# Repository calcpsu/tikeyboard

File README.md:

# Keyboard for TI Majestic Series Calculators #

1970's TI calculatore keyboards are known for failure - squishy or dead keys - leading to premature death.
As the original keyboards are generally unrepairable, this is a replacement using a PCB and micro tactile switches.
Enjoy the use of technology advanced during the mobile phone era (0.8mm thickness tact switches!).

## Details: ##

The PCB + switch comes to 2.4mm thick, which is nearly identical to the original 2.2mm thick keyboard in these calculators.

Two versions are included:
* 5 Column x 8 Row: made for a TI45, but I understand should also fit a standard TI30
* 5 Column x 9 Row: suits a TI58, TI59 programmable

## Switch Type: ##

Switches are a reasonably common SMD type (Dimensions: 4.8mm x 4.8mm x 0.8mm) available from electrical component wholesalers and elsewhere online at low cost. There is another type with a metal top cover, often sold as '1.0mm' thick, but is likely identical button underneath. These work well too (and might be a bit more durable). As long as it matches the drawing below, it should be compatible.
Some sources (apologies if links expire):
* Digikey: [PTS526 SM08 SMTR2 LFS](https://www.digikey.com.au/short/9qb5pmcp)
* Aliexpress: [100 Pcs/lot Membrane Switch 4x4x 0.8MM 4X4X0.8mm Tactile Push Button Switch Tact 4 Pin 4*4*0.8mm Switch Micro Switch SMD](https://www.aliexpress.com/item/4001331647427.html) or [SJMS 100pcs Micro Tactile Push Button Touch Tact Waterproof Switch 4x4x1 SMD 4 Pin SMT 4*4*1.0 mm Ultra thin mini Switch](https://www.aliexpress.com/item/1005001828986512.html)
* Amazon: [eMagTech 50pcs 4 Pin Patch Tact Switch Tactile Switch for Car Remote Control Key 4.8x4.8x0.8mm 4 Pin Tactile Push Button Switch Metal Plastic Switch](https://www.amazon.com.au/eMagTech-Tactile-Control-4-8x4-8x0-8mm-Plastic/dp/B0CN9467VQ)

## How to: ##

Before committing to replacing your keyboard, please consider the risks involved in working on ancient electronics. Components are sensitive to ESD, plastics and PCBs are old and susceptible to mechanical damage (hairline cracking you may not even see!). If damaged, replacement parts are typically not available at all, so damage can be irrepairable. While I have successfully replaced the keyboards on a number of my calculators, I've lost at least one calculator to ESD death during a (not keyboard related) repair attempt. As such, I cannot provide any guarantees of success but I do wish you the best of luck if you do choose to proceed. The below instructions are provided for you to undertake at your own risk.

### Building the keyboard: ###
1. Solder the tact switches to the PCB. Ensure they are accurately located (use the silkscreen layout), and flat on the PCB.
   - The switches are small and are easy to overheat when soldering - which can damage and change the feel. Use a temperature controlled iron and try to limit the heat you apply!
   - The switches need to be flat on the board, if they are raised (which can occur when soldering), the buttons will have inconsistent feel.
   - I have had some success using a tiny dab of superglue applied with a needle to locate the switches prior to soldering.
   - Do not press the switches down with any sharp objects (tweezers, screwdrivers, etc.) - this can deform the dome and again, result in inconsistent feel.
2. Solder 50mm (2in) approx. lead wires (I use copper strands from 2.5mm^2 house wiring) to each wire header, on the front (key) side of the board, extending upwards. _Note: for TI-59, the leadwires can be shorter (about 15mm is plenty)._

_Note: for Rev0, I made an error with the offset of two of the pins (R3 and R8), which is easily corrected with the lead wires. Rev1 of the board has this fixed, so it's a direct match for the original._

### Installation (Majestic series TI30/TI55/Programmer/TI45 and similar): ###
_Note: These calculators have early MOS ICs, which have no or minimal ESD protection in comparison to modern ICs. It is more important to take precautions than you might be used to with modern electronics!. Use an ESD mat and strap if you have one._
1. Open the calculator case: unclip the clips inside the battery compartment with a narrow ruler or wide screwdriver, and then push the rear case part downwards to separate front and back.
2. Desolder the original keyboard at the main board.
3. Assemble into the calculator, align all the lead wires and insert into the main board. It is imporatant to ensure the lead wires are bent/routed as per the original keyboard so the case will fit back together. This varies between calculator types.
4. Solder lead wires to main board, and trim.
5. Reassemble calculator.

### Installation (TI59 and similar): ###
The TI59 is a more complex calculator - the below instructions worked for me, please do get in touch via issues or email if you have any questions or problems.
_Note: These calculators have early MOS ICs, which have no or minimal ESD protection in comparison to modern ICs. It is more important to take precautions than you might be used to with modern electronics!. Use an ESD mat and strap if you have one._
1. Remove battery
2. Open calculator case by unscrewing the two fasteners on the back. Unclip the back case by lifting the back slightly, and sliding the back part of the case downwards to releasee the clips at the bottom.
3. Remove 2x flex cables from the card reader, noting how these are routed around the components and case.
4. Remove 4x screws from the card reader.
5. Remove the card reader and power switch by lifting out.
6. Use a small screwdriver to push up the two keyboard clips at the top of the keyboard via the cutouts in the mainboard.
7. Lift the mainboard and keyboard out from the top: take care not to lose any keys (they are loose!). Clean up as much crumbled foam as you can from the keyboard area.
8. Place the new foam pad over the keys.
9. Carefully desolder the 14 keyboard wires from the mainboard and remove the keyboard, ensuring you repair any damaged tracks and clean up flux residue (I use IPA and lots of q-tips).
10. Remove the black plastic spacer from the back of the keyboard.
11. Cut off the small locating pins from the black spacer, and sand or file these completely flush.
12. Locate the black spacer on the mainboard, and fix in place for reassembly with a very small amount of glue (e.g. superglue).
13. Fit the new keyboard to the mainboard, **leaving the wires unsoldered for the moment.**
14. Install the keyboard and mainboard into the front part of the case - slot the bottom of both in first, and gently press down the top until clipped in. Press around the mainboard to make sure everything is seated correctly.
15. Reinstall the card reader with 4x screws.
16. Check the action of the buttons, if feels ok continue, otherwise disassemble again (remove keyboard/mainboard) and see keyboard fit adjustment below.
17. Reinstall the flex cables for the card reader. Ensure the flex cable is routed correctly (as you noted previously).
18. Reinstall the back of the case by slotting into the bottom, and pressing up and down over. Take care not to damage the flex cables or components on the mainboard while doing so.
19. Reinstall the two screws on the back of the case.
20. Check the action of the buttons, if feels ok continue, otherwise disassemble again and see keyboard fit adjustment below.
21. Now solder a few of the keyboard leadwires, accessing through the back of the battery compartment. You don't need to solder them all, just enough to make sure the relative position of the keyboard and mainboard is locked in.
22. Now remove the back of the case and card reader flex cables, so you can solder and trim all the rest of the keyboard leadwires.
23. Reinstall the card reader flex cables, reinstall the back of the case.
24. Reinstall the battery (or connect to 3.3-5.0V power supply, taking care with polarity, which is marked on the mainboard) and test the keyboard/calculator works!

#### Keyboard Fit Adjustment ###
The keyboard is obviously not an exact copy of the original. The action of the small buttons is shorter than the original keyboard, and is slightly less tolerant to fit. You can adjust the fit through a number of methods, to address the two main possible problems:
1. Keys are squished with reassembly of the back of the case, and constantly pressed (particularly bottom row):
   a. Add tape or foam pieces to the front of the keyboard, to apply more pressure between the case front and the keyboard in the affected location.
   b. Make sure the spacer between the keyboard and mainboard locating posts are completely flat / fully removed. You may want to sand the spacer flat (fine - 320 grit or higher - sandpaper on the bench, rub the spacer on this a few times and observe progress until area around each pin is visibly abraded).
   c. File/sand the posts in the rear part of the case that go through the mainboard and contact the keyboard, to reduce pressure from the back of the case in the relevant locations (e.g. for bottom row issues, focus on the ones at the bottom of the case back). Don't go too far, or the key action may become loose.
2. Keys rattle or feel loose (you may have gone too far with one of the above steps):
   a. Make sure you have put that black spacer between the keyboard and mainboard. It's necessary to fully support the keyboard against the pressure from the foam pad.
   b. Apply tape or foam to the back of the keyboard in key locations (where the case back posts contact and support the keyboard) to increase pressure toward the front of the case.
   c. Consider a thicker foam pad between the keys (although this can increase the force required to press keys). It is unlikely you'll want more than 1.5mm.

## Replacing the foam:

The foam layer between the keycaps and the switches is significant to maintain the feel of the keypad. Without it, the keycaps rattle and the key feel is plasticky. It is often crumbly and degraded with age. It can be replaced with a slice of 1mm EVA foam, again widely available from craft stores and online:
* [NEW 1pcs Thickness 1/2/3/5/10mm Eva Foam Sheets Sound-Absorbing Noise Spone Foam Craft Eva Sheets Handmade Model Making Material](https://www.aliexpress.com/item/1005005567697486.html)

## Requests & PCBs:

Please do let me know if you have requests for further types.
And if you'd like a PCB or a built one, let me know - happy to provide bare PCBs, kits or assembled keyboards (to order).

Contact me at: info@calcpsu.com.au

## License

As per below, you are welcome to reproduce, amend, modify for personal use & friends.
I request you do not use this design for commercial production - i.e. no retail listings please. I'll give you a pass for a 'batch' where costs are shared.

This work is licensed under a
[Creative Commons Attribution-NonCommercial-ShareAlike 4.0 International License][cc-by-nc-sa].

[![CC BY-NC-SA 4.0][cc-by-nc-sa-image]][cc-by-nc-sa]

[cc-by-nc-sa]: http://creativecommons.org/licenses/by-nc-sa/4.0/
[cc-by-nc-sa-image]: https://licensebuttons.net/l/by-nc-sa/4.0/88x31.png
[cc-by-nc-sa-shield]: https://img.shields.io/badge/License-CC%20BY--NC--SA%204.0-lightgrey.svg

## The paitent: ##
A TI-45, the only Majestic with a VFD display, available in the European market.
Unusual, as most of this series had LED displays.

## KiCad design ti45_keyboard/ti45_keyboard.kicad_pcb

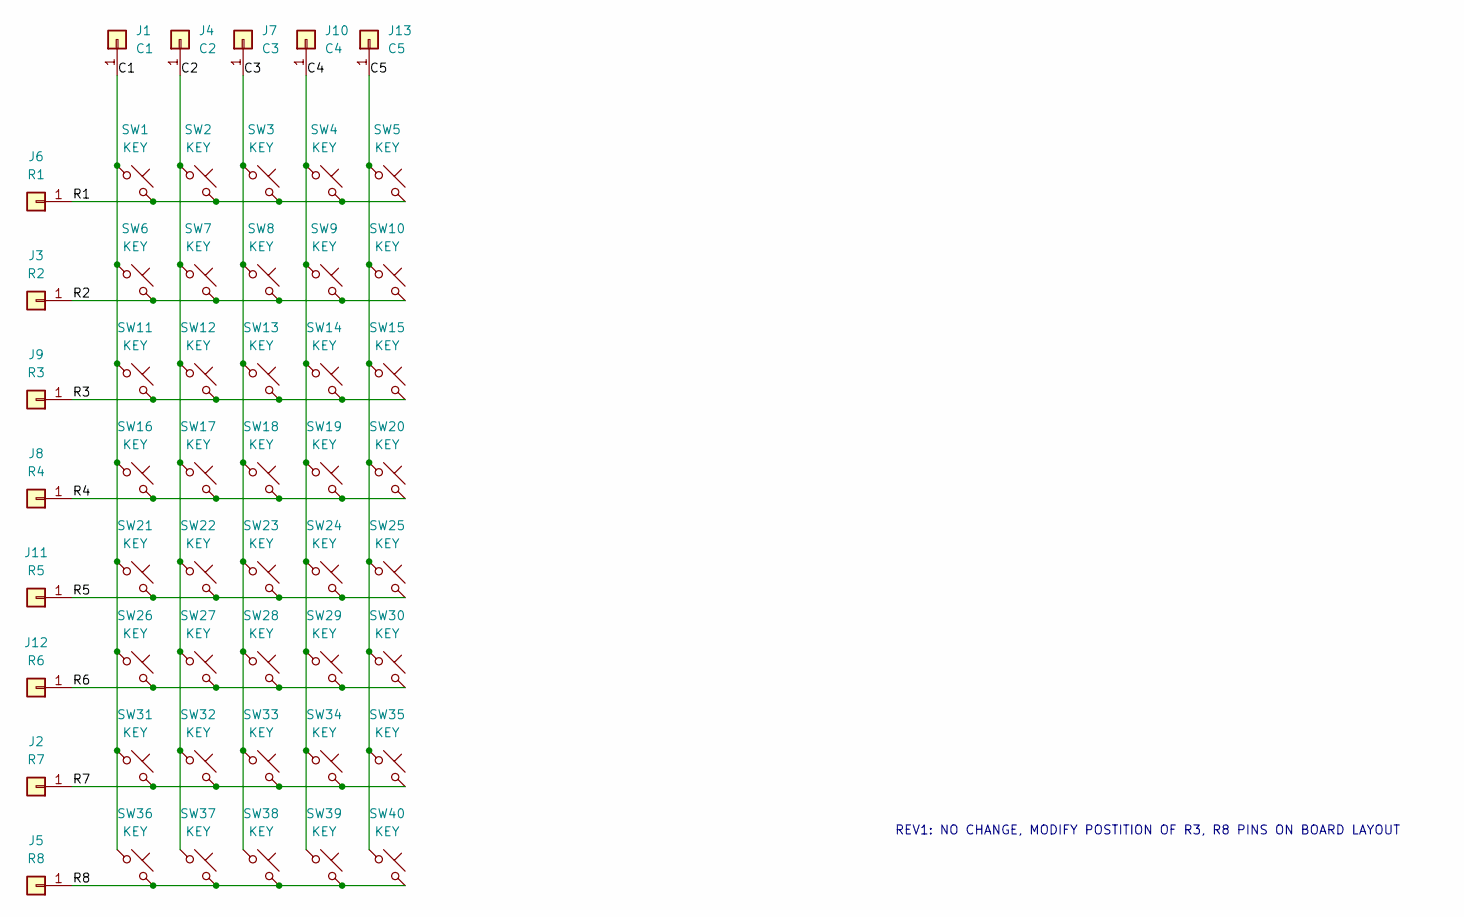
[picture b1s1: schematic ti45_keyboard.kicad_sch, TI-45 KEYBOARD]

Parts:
J1: C1; SolderWire-0.25sqmm_1x01_D0.65mm_OD1.7mm
J2: R7; SolderWire-0.25sqmm_1x01_D0.65mm_OD1.7mm
J3: R2; SolderWire-0.25sqmm_1x01_D0.65mm_OD1.7mm
J4: C2; SolderWire-0.25sqmm_1x01_D0.65mm_OD1.7mm
J5: R8; SolderWire-0.25sqmm_1x01_D0.65mm_OD1.7mm
J6: R1; SolderWire-0.25sqmm_1x01_D0.65mm_OD1.7mm
J7: C3; SolderWire-0.25sqmm_1x01_D0.65mm_OD1.7mm
J8: R4; SolderWire-0.25sqmm_1x01_D0.65mm_OD1.7mm
J9: R3; SolderWire-0.25sqmm_1x01_D0.65mm_OD1.7mm
J10: C4; SolderWire-0.25sqmm_1x01_D0.65mm_OD1.7mm
J11: R5; SolderWire-0.25sqmm_1x01_D0.65mm_OD1.7mm
J12: R6; SolderWire-0.25sqmm_1x01_D0.65mm_OD1.7mm
J13: C5; SolderWire-0.25sqmm_1x01_D0.65mm_OD1.7mm
SW1, SW2, SW3, SW4, SW5, SW6, SW7, SW8, SW9, SW10, SW11, SW12, SW13, SW14, SW15, SW16, SW17, SW18, SW19, SW20, SW21, SW22, SW23, SW24, SW25, SW26, SW27, SW28, SW29, SW30, SW31, SW32, SW33, SW34, SW35, SW36, SW37, SW38, SW39, SW40: KEY; PUSH_TACT_4.8x4.8x0.8

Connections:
/C1: J1.1, SW1.1, SW6.1, SW11.1, SW16.1, SW21.1, SW26.1, SW31.1, SW36.1
/C2: J4.1, SW2.1, SW7.1, SW12.1, SW17.1, SW22.1, SW27.1, SW32.1, SW37.1
/C3: J7.1, SW3.1, SW8.1, SW13.1, SW18.1, SW23.1, SW28.1, SW33.1, SW38.1
/C4: J10.1, SW4.1, SW9.1, SW14.1, SW19.1, SW24.1, SW29.1, SW34.1, SW39.1
/C5: J13.1, SW5.1, SW10.1, SW15.1, SW20.1, SW25.1, SW30.1, SW35.1, SW40.1
/R1: J6.1, SW1.2, SW2.2, SW3.2, SW4.2, SW5.2
/R2: J3.1, SW6.2, SW7.2, SW8.2, SW9.2, SW10.2
/R3: J9.1, SW11.2, SW12.2, SW13.2, SW14.2, SW15.2
/R4: J8.1, SW16.2, SW17.2, SW18.2, SW19.2, SW20.2
/R5: J11.1, SW21.2, SW22.2, SW23.2, SW24.2, SW25.2
/R6: J12.1, SW26.2, SW27.2, SW28.2, SW29.2, SW30.2
/R7: J2.1, SW31.2, SW32.2, SW33.2, SW34.2, SW35.2
/R8: J5.1, SW36.2, SW37.2, SW38.2, SW39.2, SW40.2

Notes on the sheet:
REV1: NO CHANGE, MODIFY POSTITION OF R3, R8 PINS ON BOARD LAYOUT

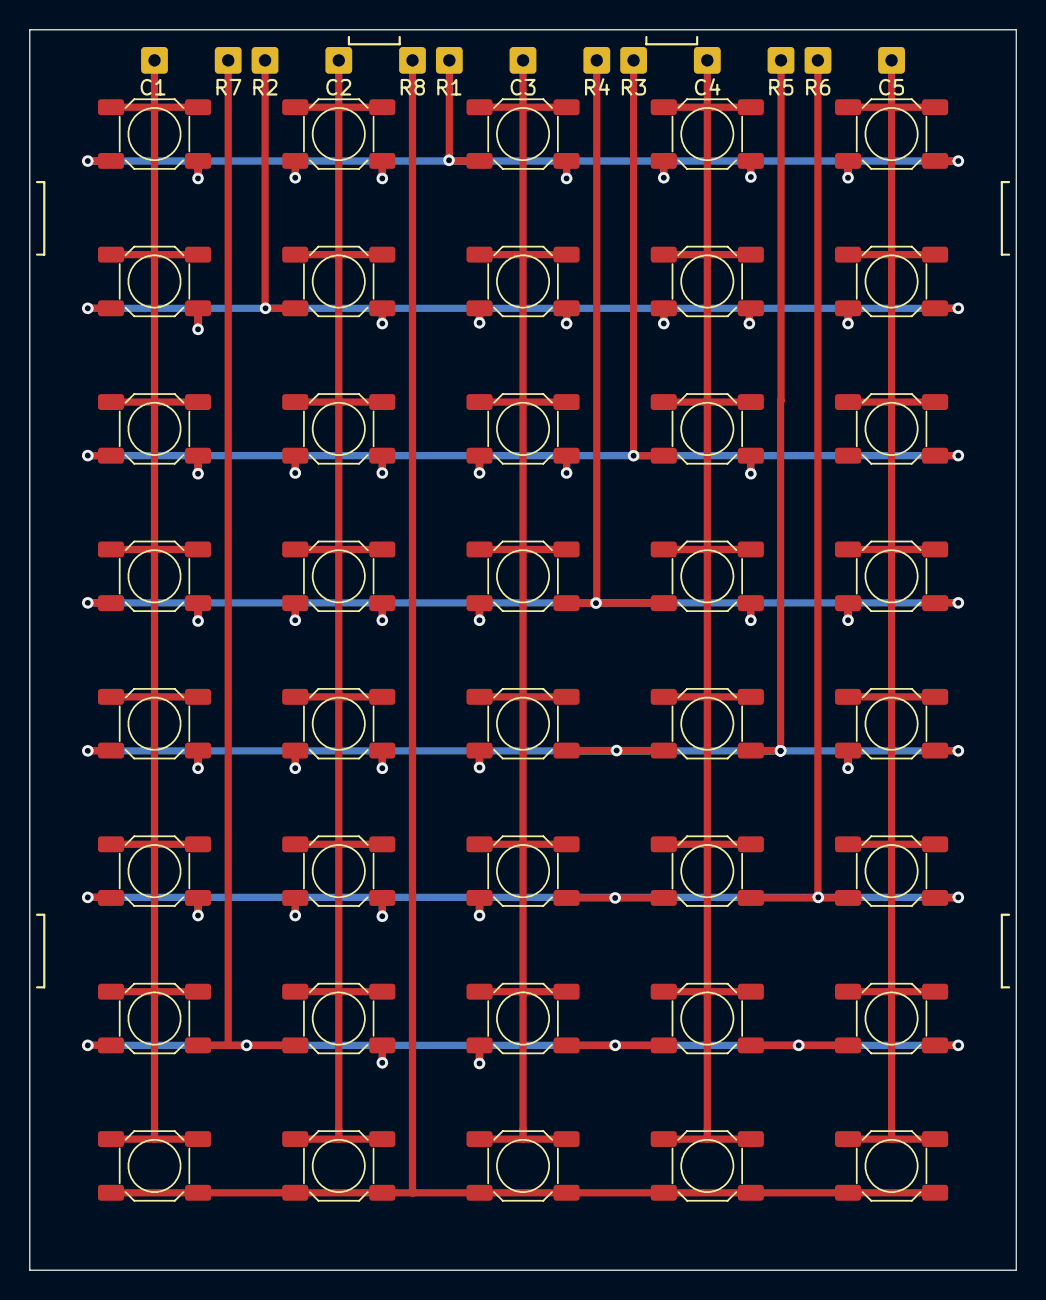
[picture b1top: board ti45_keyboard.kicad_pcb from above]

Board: 2 copper layers, 68.0 x 85.5 mm, 53 parts (0 on the bottom side), 13 nets.

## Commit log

2024-09-08 ti45 initial commit (rev1)
2024-09-08 ti59 initial commit (rev1)
2024-09-09 images
2024-09-09 update images
2025-01-18 Correct error with R2 missing track
2025-01-18 Add dimensions to PCB layout
